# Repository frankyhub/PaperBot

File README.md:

<div align="center">

|[:skull:ISSUE](https://github.com/frankyhub/PaperBot/issues?q=is%3Aissue)|[:speech_balloon: Forum /Discussion](https://github.com/frankyhub/PaperBot/discussions)|[:grey_question:WiKi](https://github.com/frankyhub/PaperBot/wiki)||
|--|--|--|--|
| | | | |
<a href="https://github.com/frankyhub/PaperBot/issues">|<a href="https://github.com/frankyhub/PaperBot/discussions">|<a href="https://github.com/frankyhub/PaperBot/6eleases">||
|| <a href="https://github.com/frankyhub/PaperBot/pulse" alt="Activity">| <a href="https://github.com/frankyhub/PaperBot/graphs/traffic">  |<a href="https://github.com/frankyhub?tab=stars"> ||

<br> <br>

</div>

Platine mit NE555 blink-LEDs

<br> <br>
  
<br> <br>

Platine mit RGB-LEDs
<br> <br>

<br> <br>

---

<div style="position:absolute; left:2cm; ">   
<ol class="breadcrumb" style="border-top: 2px solid black;border-bottom:2px solid black; height: 45px; width: 900px;"> <p align="center"><a href="#oben">nach oben</a></p></ol>
</div>  

---

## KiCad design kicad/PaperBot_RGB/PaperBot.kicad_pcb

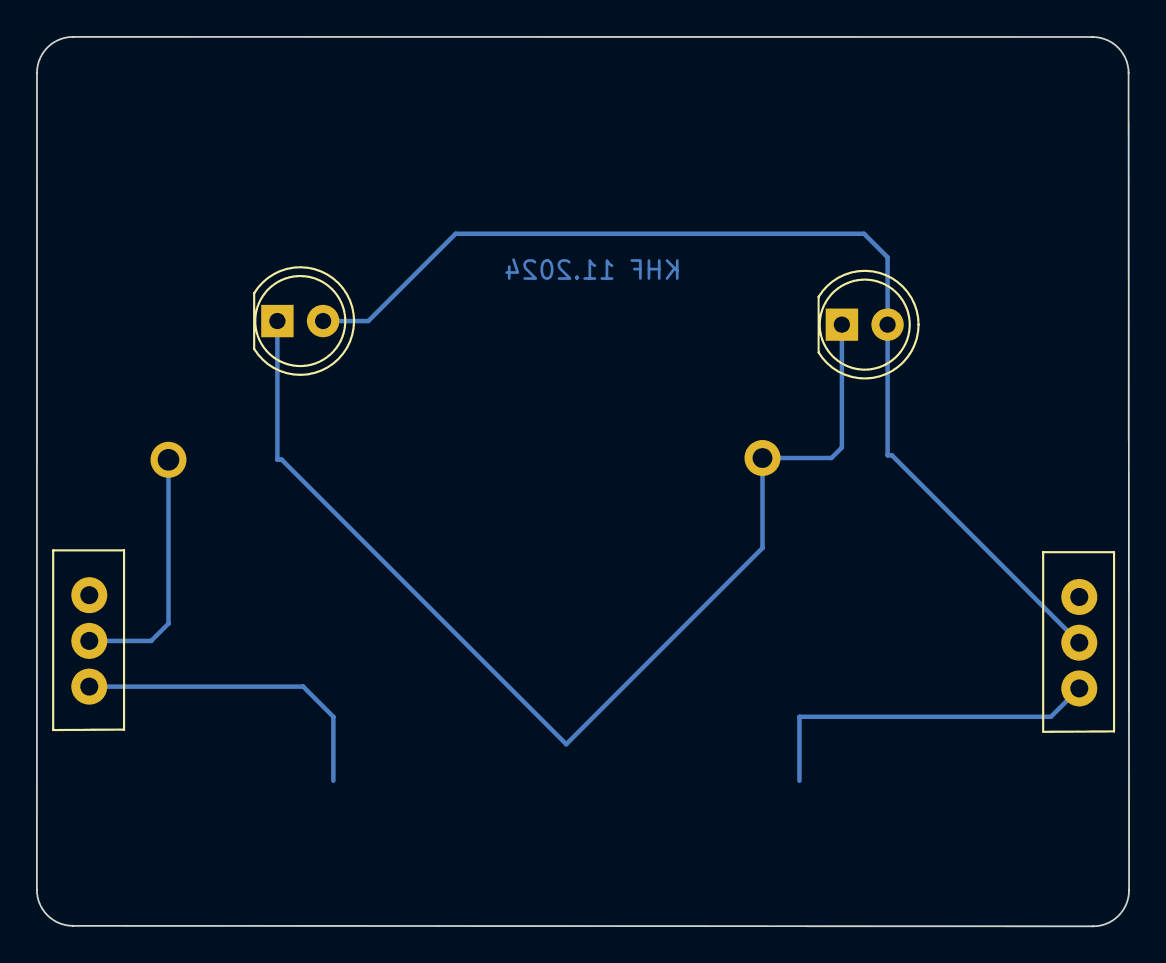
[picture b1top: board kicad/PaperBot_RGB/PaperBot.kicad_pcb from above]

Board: 2 copper layers, 60.7 x 49.4 mm, 7 parts (1 on the bottom side), 3 nets.

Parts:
D1, D2: LED; LED_D5.0mm
M+: LP_rund
M-: LP_rund
S1, S2: Micro_Schalter; Micro_SchalterKHF
U2: BAT_HLD_SMD; BAT-HLD-SMD-Blech

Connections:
unnamed: D1.2 (A), D2.2 (A), M+.1, S1.2 (E), S2.2 (E)
unnamed: D1.1 (K), D2.1 (K), M-.1, U2.2
unnamed: S1.1 (A), S2.1 (A), U2.1

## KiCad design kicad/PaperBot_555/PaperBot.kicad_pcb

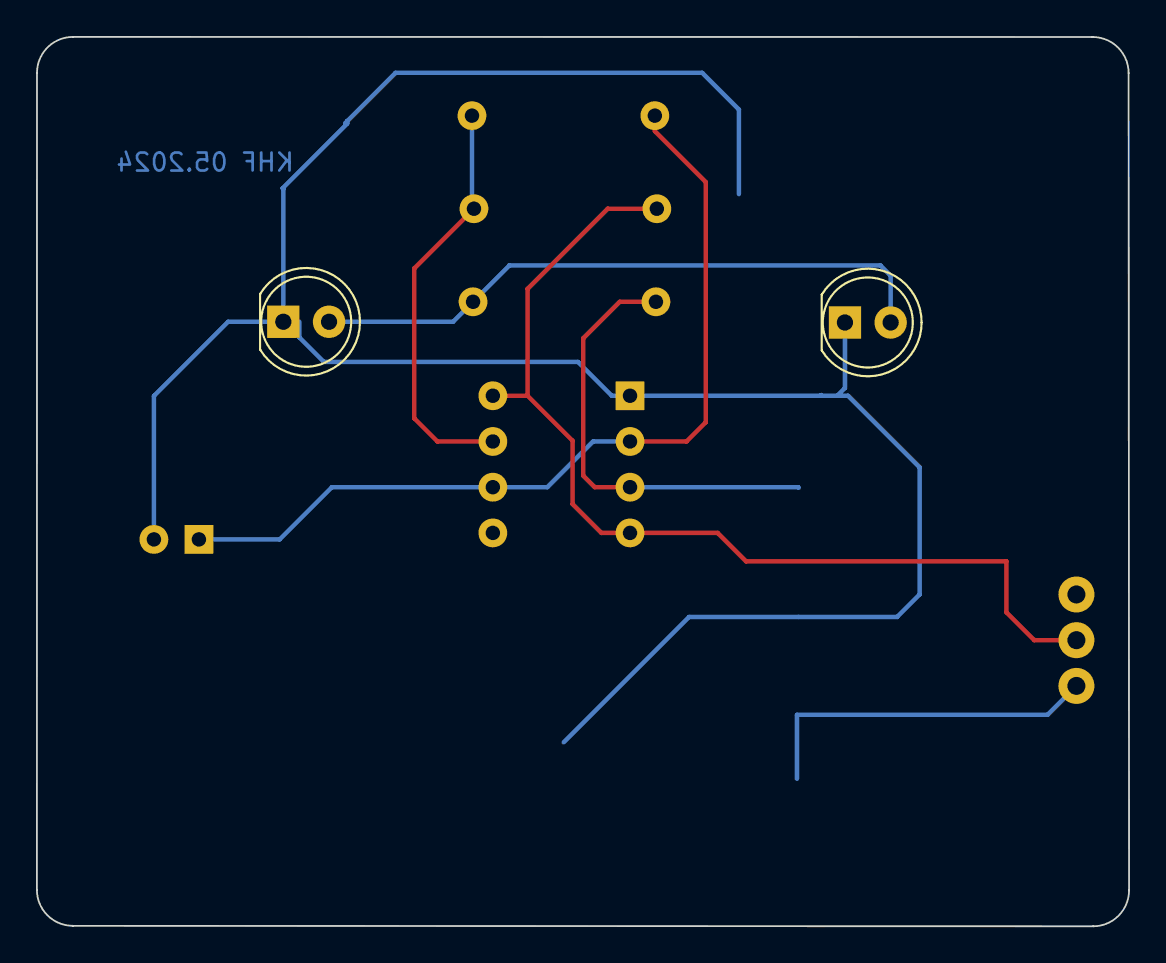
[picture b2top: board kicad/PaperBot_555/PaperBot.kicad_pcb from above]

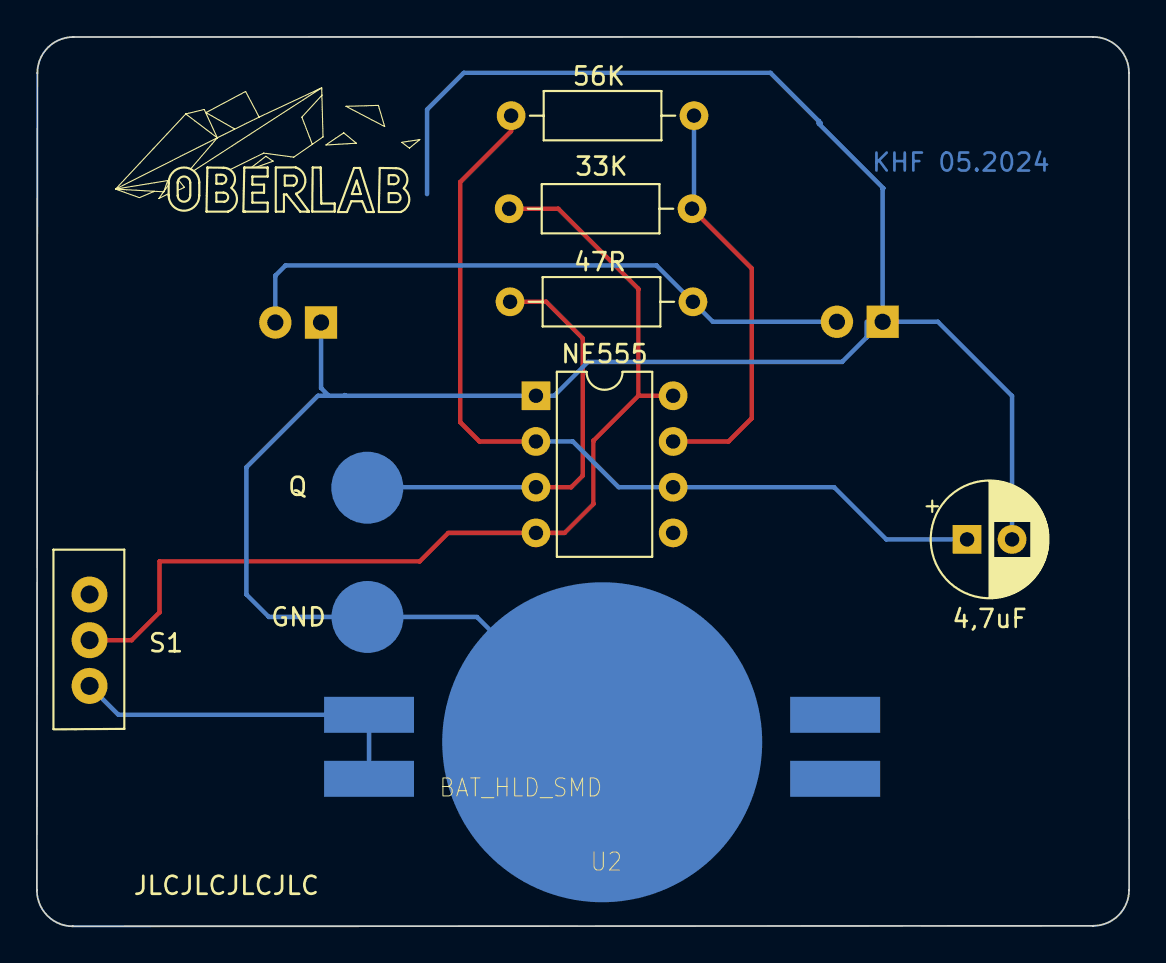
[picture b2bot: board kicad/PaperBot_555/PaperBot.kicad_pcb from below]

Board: 2 copper layers, 60.7 x 49.4 mm, 10 parts (8 on the bottom side), 6 nets.

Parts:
C1: 4,7uF; CP_Radial_D6.3mm_P2.50mm
D1, D2: LED; LED_D5.0mm
GND: Q; LP
NE555: NE555P; DIP-8_W7.62mm
R1: 56K; R_Axial_DIN0207_L6.3mm_D2.5mm_P10.16mm_Horizontal
R2: 33K; R_Axial_DIN0207_L6.3mm_D2.5mm_P10.16mm_Horizontal
R3: 47R; R_Axial_DIN0207_L6.3mm_D2.5mm_P10.16mm_Horizontal
S1: Micro_Schalter; Micro_SchalterKHF
U2: BAT_HLD_SMD; BAT-HLD-SMD-Blech

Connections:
unnamed: D1.2 (A), D2.2 (A), R3.2
unnamed: C1.2, D1.1 (K), D2.1 (K), GND.1, NE555.1 (GND), U2.2
unnamed: NE555.4 (R), NE555.8 (VCC), R2.1, S1.2 (E)
unnamed: NE555.7 (DIS), R1.2, R2.2
unnamed: NE555.3 (Q), R3.1
unnamed: C1.1, NE555.2 (TR), NE555.6 (THR), R1.1

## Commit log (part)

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2024-07-02 V 02.07.2024
2024-08-22 V 22.08.2024
2024-08-25 V 25.08.2024
2024-10-07 V 07102024
2024-10-12 V12102024
2024-11-19 V 19.11.2024
2024-11-20 V20112024
